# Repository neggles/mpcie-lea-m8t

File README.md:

# mPCIe-LEA-M8T

This is a little miniPCIe card I designed to hold a [u-blox LEA-M8T](https://www.u-blox.com/en/product/neolea-m8t-series) GNSS module, with an IO header and an optional backup supercap.
The IO header has both timepulse outputs, as well as UART TX/RX. Module USB is connected to miniPCIe USB. I have not included a way to switch from UART to SPI.

I had this made by [JLCPCB](https://jlcpcb.com) using their 1mm thick PCBs, and elected to get them to assemble most of it - while all of the parts except the supercapacitor, connectors, and GNSS module are in their extended part library, it didn't make sense to spend $6 on extended part fees for two assembled boards, so I skipped the transistors and diode.

## Repository Structure
- `mPCIe-GNSS` contains the main schematics and board drawing
- `mPCIe-GNSS/mPCIe-GNSS.pretty` contains the board-specific footprints
- `mPCIe-GNSS/mPCIe-GNSS-archive.lib` contains the board-specific symbols

## Building
Simply call `make` in the top-top level directory. The `build` directory will
them contain:

- the main mPCIe board
- A panelized version of said board
- zipped gerbers for the boards you can directly use for manufacturing
- zipped gerbers and SMT assembly BOM/position files for JLCPCB's SMT assembly service for the single-board version.

Makefile uses [Jan Mrázek](https://github.com/yaqwsx)'s [KiKit](https://github.com/yaqwsx/KiKit), which I cannot recommend enough, and therefore has to be available on your system.

Jan's [jlcparts](https://yaqwsx.github.io/jlcparts/) app was also extremely useful in narrowing down part choices based on what JLCPCB have available.

-----
### **IMPORTANT NOTE:** If you give JLCPCB these files as-is, *please* verify the orientation of every part before submitting.
Furthermore, while I have received a run of these from JLCPCB, but I appear to have killed my LEA-M8T while 'recovering' it from a chunk of PCB, so **I can't verify that they *actually work***. Will update this if that changes.

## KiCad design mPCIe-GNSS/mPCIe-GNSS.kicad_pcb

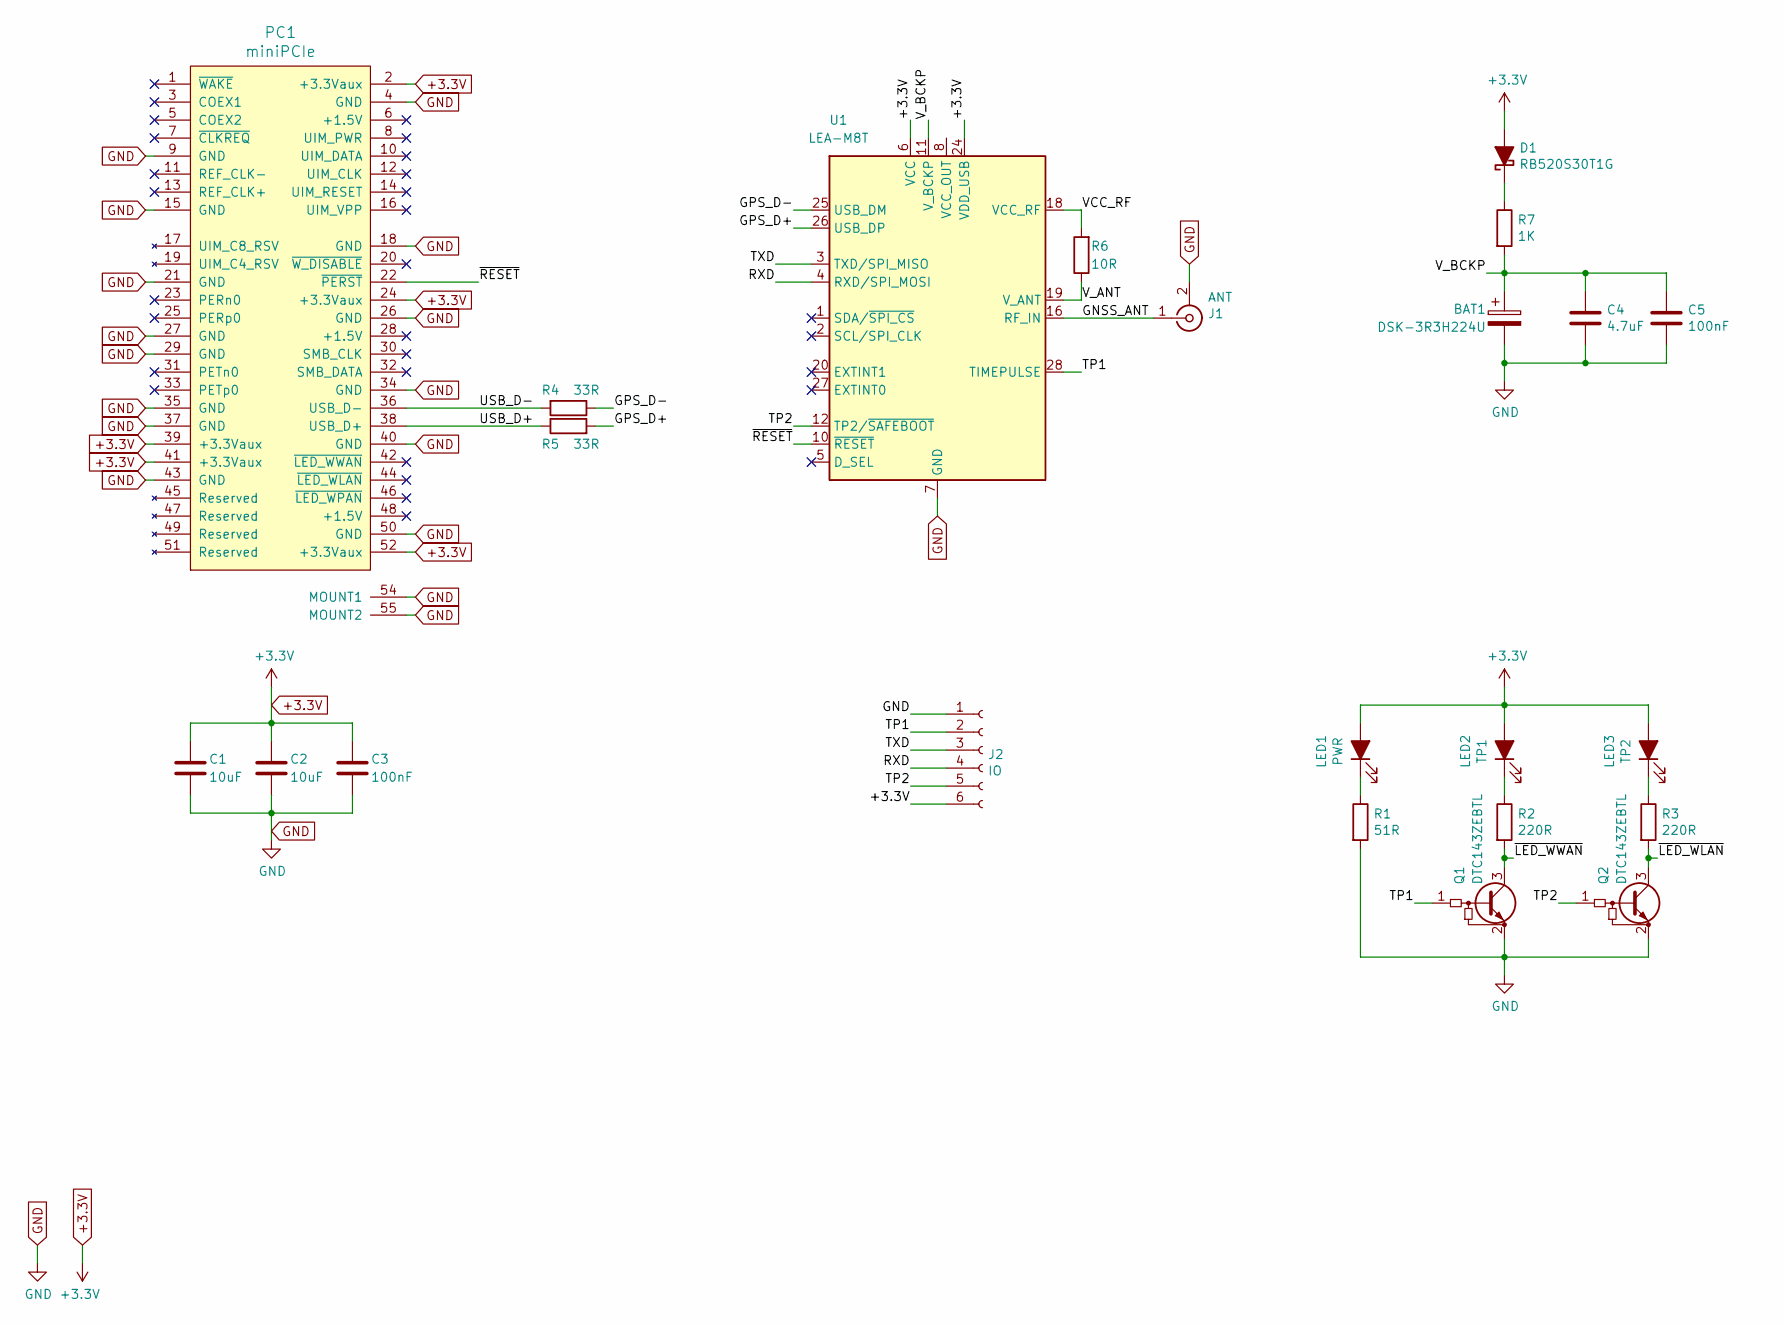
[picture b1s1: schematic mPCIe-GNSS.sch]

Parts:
BAT1: DSK-3R3H224U; CAP_DSK-3R3H224U-HL
C1, C2: 10uF; C_0603_1608Metric; LCSC C19702
C3: 100nF; C_0603_1608Metric; LCSC C14663
C4: 4.7uF; C_0402_1005Metric; LCSC C23733
C5: 100nF; C_0402_1005Metric; LCSC C1525
D1: RB520S30T1G; D_SOD-523; LCSC C154821
J1: ANT; U.FL_Hirose_U.FL-R-SMT-1_Vertical_Tweaked
J2: IO; JST_SH_SM06B-SRSS-TB_1x06-1MP_P1.00mm_Horizontal_3D
LED1: PWR; LED_0603_1608Metric_SnapModel; LCSC C72041
LED2: TP1; LED_0603_1608Metric_SnapModel; LCSC C72038
LED3: TP2; LED_0603_1608Metric_SnapModel; LCSC C2286
PC1: miniPCIe; mini-PCIe_F1_Full_v517
Q1, Q2: DTC143ZEBTL; Q_EMT3F; LCSC C172398
R1: 51R; R_0402_1005Metric; LCSC C25125
R2, R3: 220R; R_0402_1005Metric; LCSC C25091
R4, R5: 33R; R_0402_1005Metric; LCSC C25105
R6: 10R; R_0603_1608Metric; LCSC C22859
R7: 1K; R_0402_1005Metric; LCSC C11702
U1: LEA-M8T; ublox_LEA; PARTREV R05

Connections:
+3.3V: C1.2, C2.2, C3.1, D1.2 (A), J2.6, LED1.2 (A), LED2.2 (A), LED3.2 (A), PC1.2 (+3.3Vaux), PC1.24 (+3.3Vaux), PC1.39 (+3.3Vaux), PC1.41 (+3.3Vaux), PC1.52 (+3.3Vaux), U1.6 (VCC), U1.24 (VDD_USB)
/GNSS_ANT: J1.1 (In), U1.16 (RF_IN)
/GPS_D+: R5.2, U1.26 (USB_DP)
/GPS_D-: R4.1, U1.25 (USB_DM)
/RXD: J2.4, U1.4 (RXD/SPI_MOSI)
/TP1: J2.2, Q1.1 (B), U1.28 (TIMEPULSE)
/TP2: J2.5, Q2.1 (B), U1.12 (TP2/~SAFEBOOT)
/TXD: J2.3, U1.3 (TXD/SPI_MISO)
/USB_D+: PC1.38 (USB_D+), R5.1
/USB_D-: PC1.36 (USB_D-), R4.2
/VCC_RF: R6.2, U1.18 (VCC_RF)
/V_ANT: R6.1, U1.19 (V_ANT)
/V_BCKP: BAT1.1, C4.1, C5.1, R7.2, U1.11 (V_BCKP)
/~LED_WLAN: Q2.3 (C), R3.2
/~LED_WWAN: Q1.3 (C), R2.2
/~RESET: PC1.22 (~PERST), U1.10 (~RESET)
GND: BAT1.2, C1.1, C2.1, C3.2, C4.2, C5.2, J1.2 (Ext), J2.1, PC1.4 (GND), PC1.9 (GND), PC1.15 (GND), PC1.18 (GND), PC1.21 (GND), PC1.26 (GND), PC1.27 (GND), PC1.29 (GND), PC1.34 (GND), PC1.35 (GND), PC1.37 (GND), PC1.40 (GND), PC1.43 (GND), PC1.50 (GND), PC1.54 (MOUNT1), PC1.55 (MOUNT2), Q1.2 (E), Q2.2 (E), R1.2, U1.7 (GND), U1.13 (GND), U1.14 (GND), U1.15 (GND), U1.17 (GND)
unnamed: D1.1 (K), R7.1
unnamed: LED1.1 (K), R1.1
unnamed: LED2.1 (K), R2.1
unnamed: LED3.1 (K), R3.1

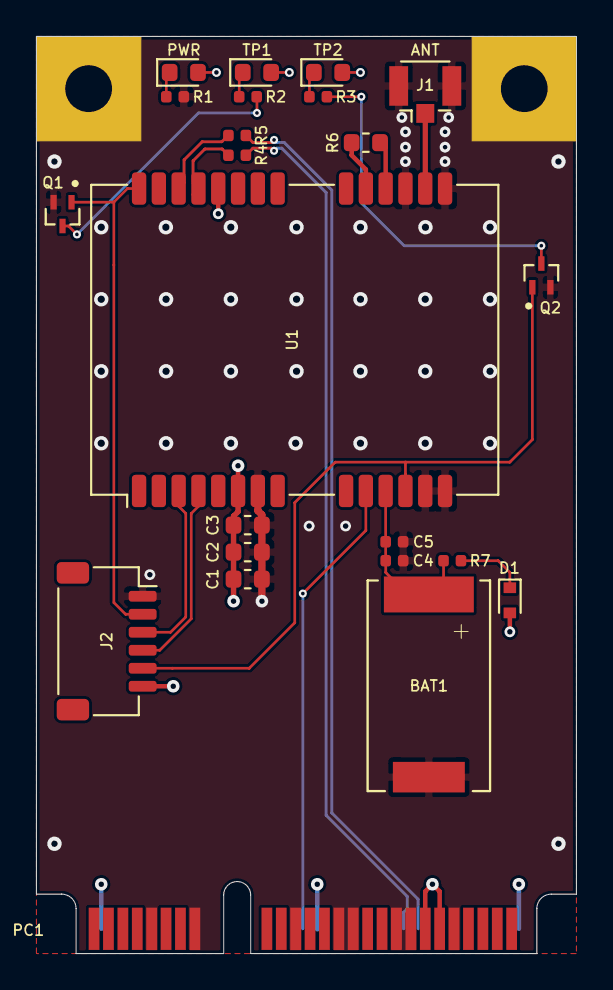
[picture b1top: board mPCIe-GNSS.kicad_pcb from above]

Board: 4 copper layers, 30.0 x 51.0 mm, 23 parts (0 on the bottom side), 21 nets.

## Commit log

2021-01-23 add files
2021-01-23 embed image
2021-02-08 updoots
2021-02-08 update makefile and readme
2021-02-08 trigger travis for pages
2021-02-08 add stepfiles, update gitignore
2021-02-08 update README and makefile
2021-02-08 add badge
2021-02-08 update makefile for panel, i derped
2021-02-08 Deploy neg2led/mpcie-lea-m8t to github.com/neg2led/mpcie-lea-m8t.git:gh-pages
